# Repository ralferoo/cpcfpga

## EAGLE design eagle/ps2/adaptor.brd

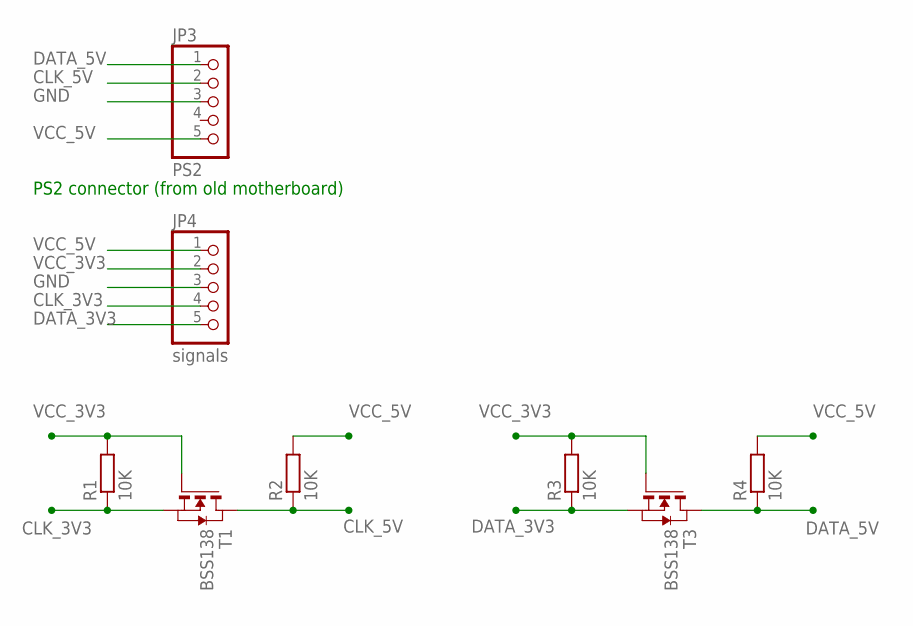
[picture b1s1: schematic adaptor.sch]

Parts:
JP3: PS2; 1X05
JP4: signals; 1X05
R1, R2, R3, R4: 10K; R0805
T1, T3: BSS138; SOT-23

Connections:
CLK_3V3: JP4.4, R1.1, T1.2 (S)
CLK_5V: JP3.2, R2.1, T1.1 (D)
DATA_3V3: JP4.5, R3.1, T3.2 (S)
DATA_5V: JP3.1, R4.1, T3.1 (D)
GND: JP3.3, JP4.3
VCC_3V3: JP4.2, R1.2, R3.2, T1.3 (G), T3.3 (G)
VCC_5V: JP3.5, JP4.1, R2.2, R4.2

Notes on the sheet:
PS2 connector (from old motherboard)

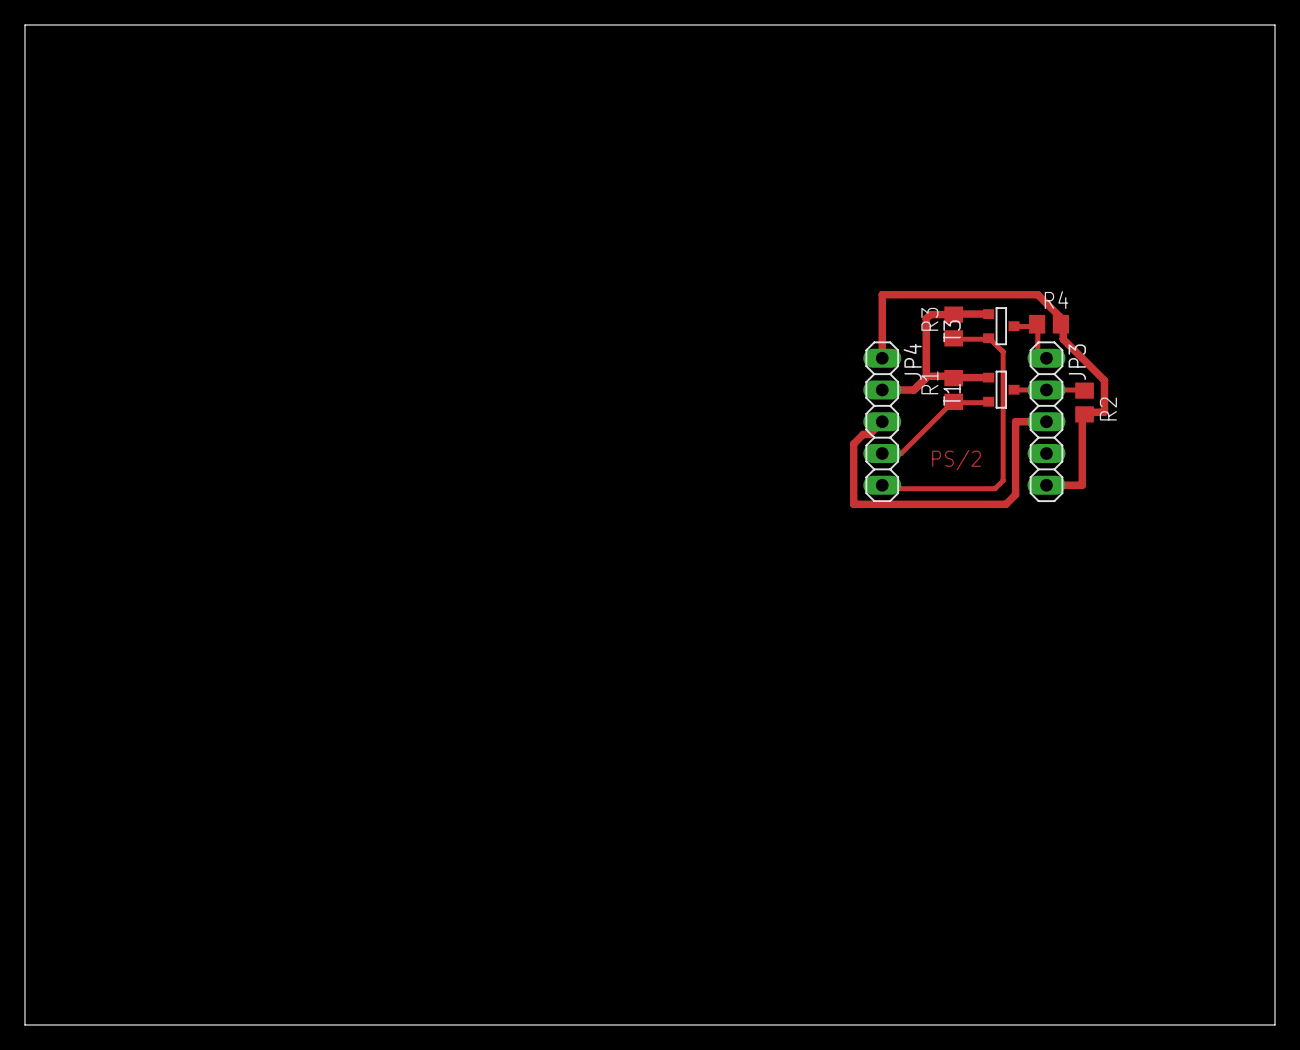
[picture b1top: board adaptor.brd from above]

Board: 2 copper layers, 100.0 x 80.0 mm, 8 parts (0 on the bottom side), 7 nets.

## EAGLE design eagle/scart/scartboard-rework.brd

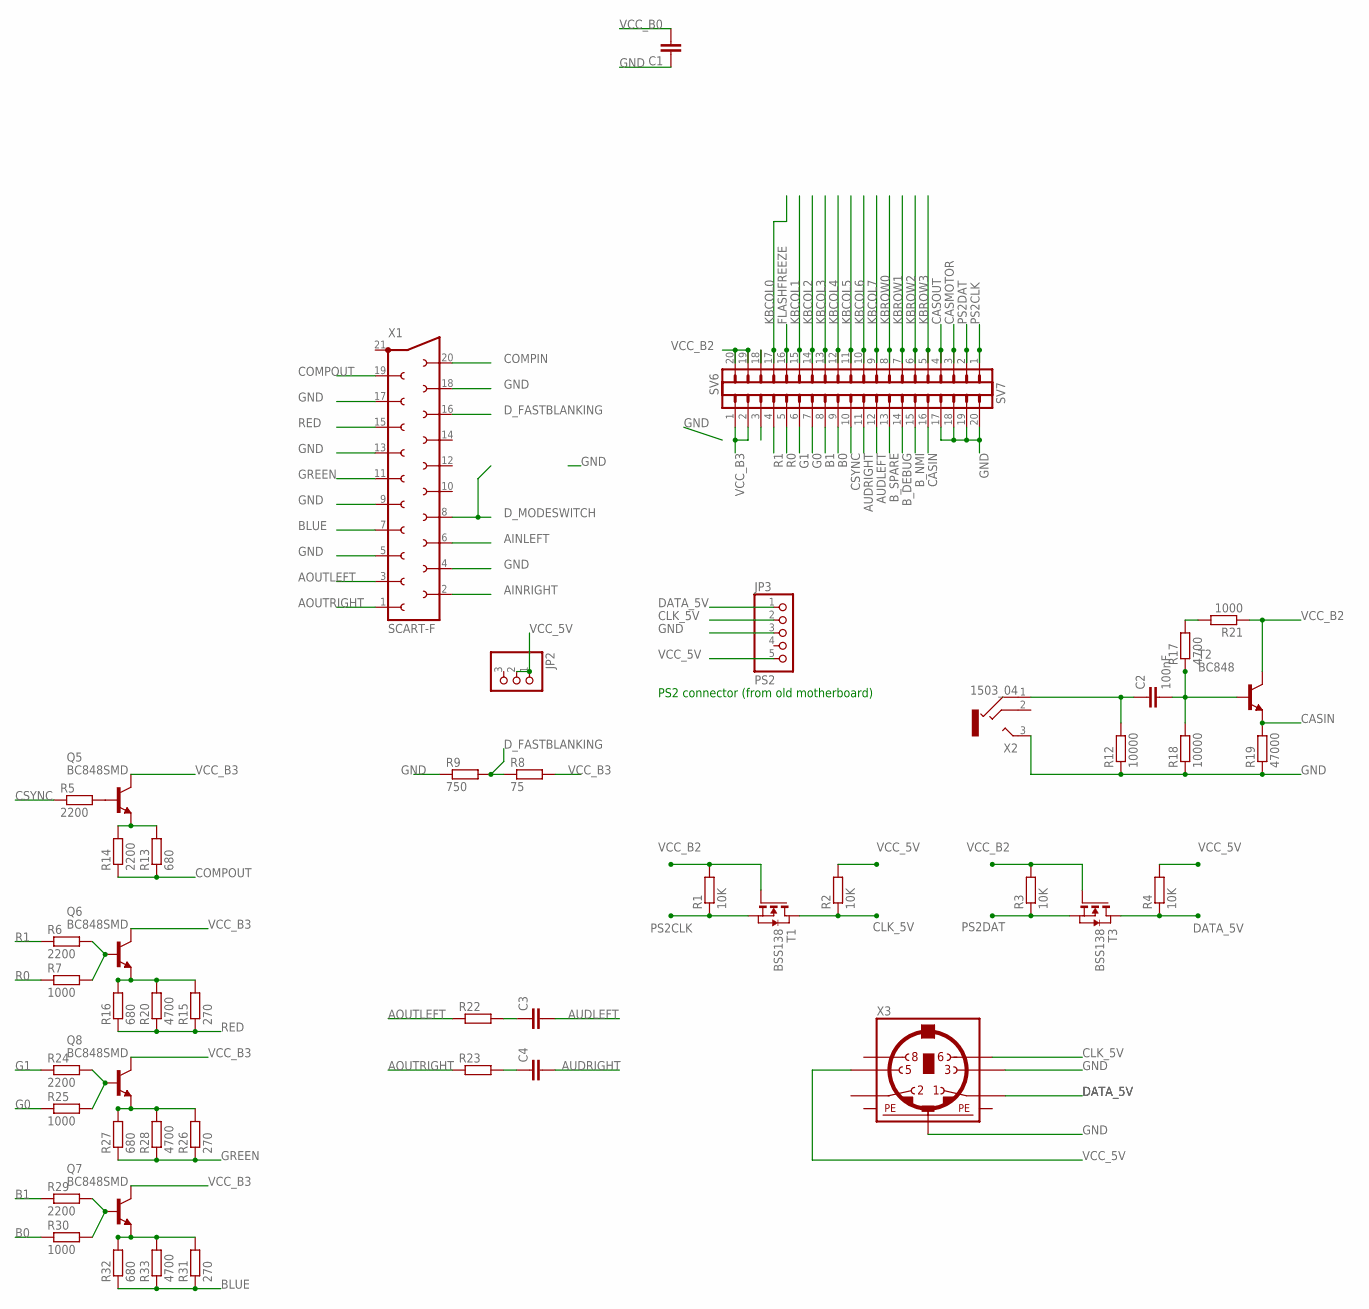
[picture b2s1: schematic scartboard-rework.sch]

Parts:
C1, C3, C4: C-EUC0603; C0603
C2: 100nF; C0603
JP2: PINHD-1X3; 1X03
JP3: PS2; 1X05
Q5, Q6, Q7, Q8: BC848SMD; SOT23
R1, R2, R3, R4: 10K; R0805
R5, R6, R14, R24, R29: 2200; R0805
R7, R21, R25, R30: 1000; R0805
R8: 75; R0805
R9: 750; R0805
R12, R18: 10000; R0805
R13, R16, R27, R32: 680; R0805
R15, R26, R31: 270; R0805
R17, R20, R28, R33: 4700; R0805
R19: 47000; R0805
R22, R23: R-EU_M0805; M0805
SV6, SV7: MA20-1
T1, T3: BSS138; SOT-23
T2: BC848; SOT23
X1: SCART-F
X2: 1503_04
X3: MINI_DIN_6; M_DIN6

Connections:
AINLEFT: X1.6
AINRIGHT: X1.2
AOUTLEFT: R22.1, X1.3
AOUTRIGHT: R23.1, X1.1
AUDLEFT: C3.2, SV7.12
AUDRIGHT: C4.2, SV7.11
B0: R30.1, SV7.9
B1: R29.1, SV7.8
BLUE: R31.1, R32.1, R33.1, X1.7
B_DEBUG: SV7.14
B_NMI: SV7.15
B_SPARE: SV7.13
CASIN: R19.2, SV7.16, T2.2 (E)
CASMOTOR: SV6.3
CASOUT: SV6.4
CLK_5V: JP3.2, R2.1, T1.1 (D), X3.6
COMPIN: X1.20
COMPOUT: R13.1, R14.1, X1.19
CSYNC: R5.1, SV7.10
DATA_5V: JP3.1, R4.1, T3.1 (D), X3.1
D_FASTBLANKING: R8.1, R9.2, X1.16
D_MODESWITCH: X1.8
FLASHFREEZE: SV6.16
G0: R25.1, SV7.7
G1: R24.1, SV7.6
GND: C1.1, JP3.3, R9.1, R12.1, R18.1, R19.1, SV7.17, SV7.18, SV7.19, SV7.20, X1.4, X1.5, X1.9, X1.13, X1.17, X1.18, X2.3 (2), X3.3, X3.SH2 (PE2)
GREEN: R26.1, R27.1, R28.1, X1.11
KBCOL0: SV6.17
KBCOL1: SV6.15
KBCOL2: SV6.14
KBCOL3: SV6.13
KBCOL4: SV6.12
KBCOL5: SV6.11
KBCOL6: SV6.10
KBCOL7: SV6.9
KBROW0: SV6.8
KBROW1: SV6.7
KBROW2: SV6.6
KBROW3: SV6.5
unnamed: Q5.2 (E), R13.2, R14.2
unnamed: Q6.1 (B), R6.2, R7.2
unnamed: Q5.1 (B), R5.2
unnamed: Q6.2 (E), R15.2, R16.2, R20.2
unnamed: C2.2, R17.1, R18.2, T2.1 (B)
unnamed: Q8.1 (B), R24.2, R25.2
unnamed: Q8.2 (E), R26.2, R27.2, R28.2
unnamed: Q7.1 (B), R29.2, R30.2
unnamed: Q7.2 (E), R31.2, R32.2, R33.2
unnamed: R17.2, R21.2
unnamed: C2.1, R12.2, X2.1
unnamed: C3.1, R22.2
unnamed: C4.1, R23.2
PE1: X3.SH1 (PE1)
PE3: X3.SH3 (PE3)
PS2CLK: R1.1, SV6.1, T1.2 (S)
PS2DAT: R3.1, SV6.2, T3.2 (S)
R0: R7.1, SV7.5
R1: R6.1, SV7.4
RED: R15.1, R16.1, R20.1, X1.15
VCC_5V: JP2.1, JP2.2, JP3.5, R2.2, R4.2, X3.5
VCC_B0: C1.2
VCC_B2: R1.2, R3.2, R21.1, SV6.19, SV6.20, T1.3 (G), T2.3 (C), T3.3 (G)
VCC_B3: Q5.3 (C), Q6.3 (C), Q7.3 (C), Q8.3 (C), R8.2, SV7.1, SV7.2

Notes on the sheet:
PS2 connector (from old motherboard)

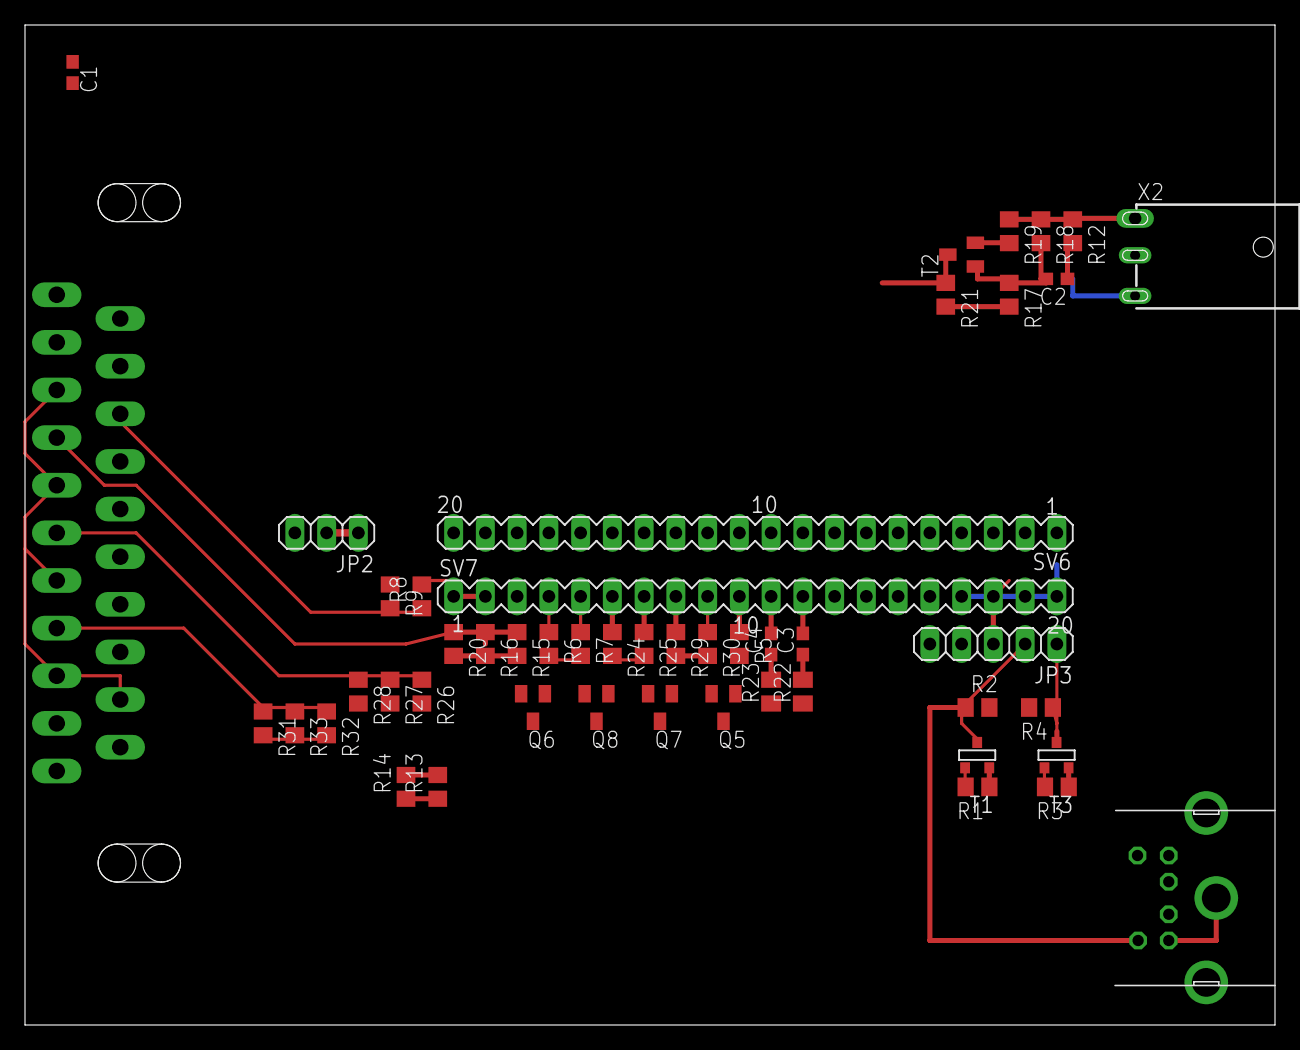
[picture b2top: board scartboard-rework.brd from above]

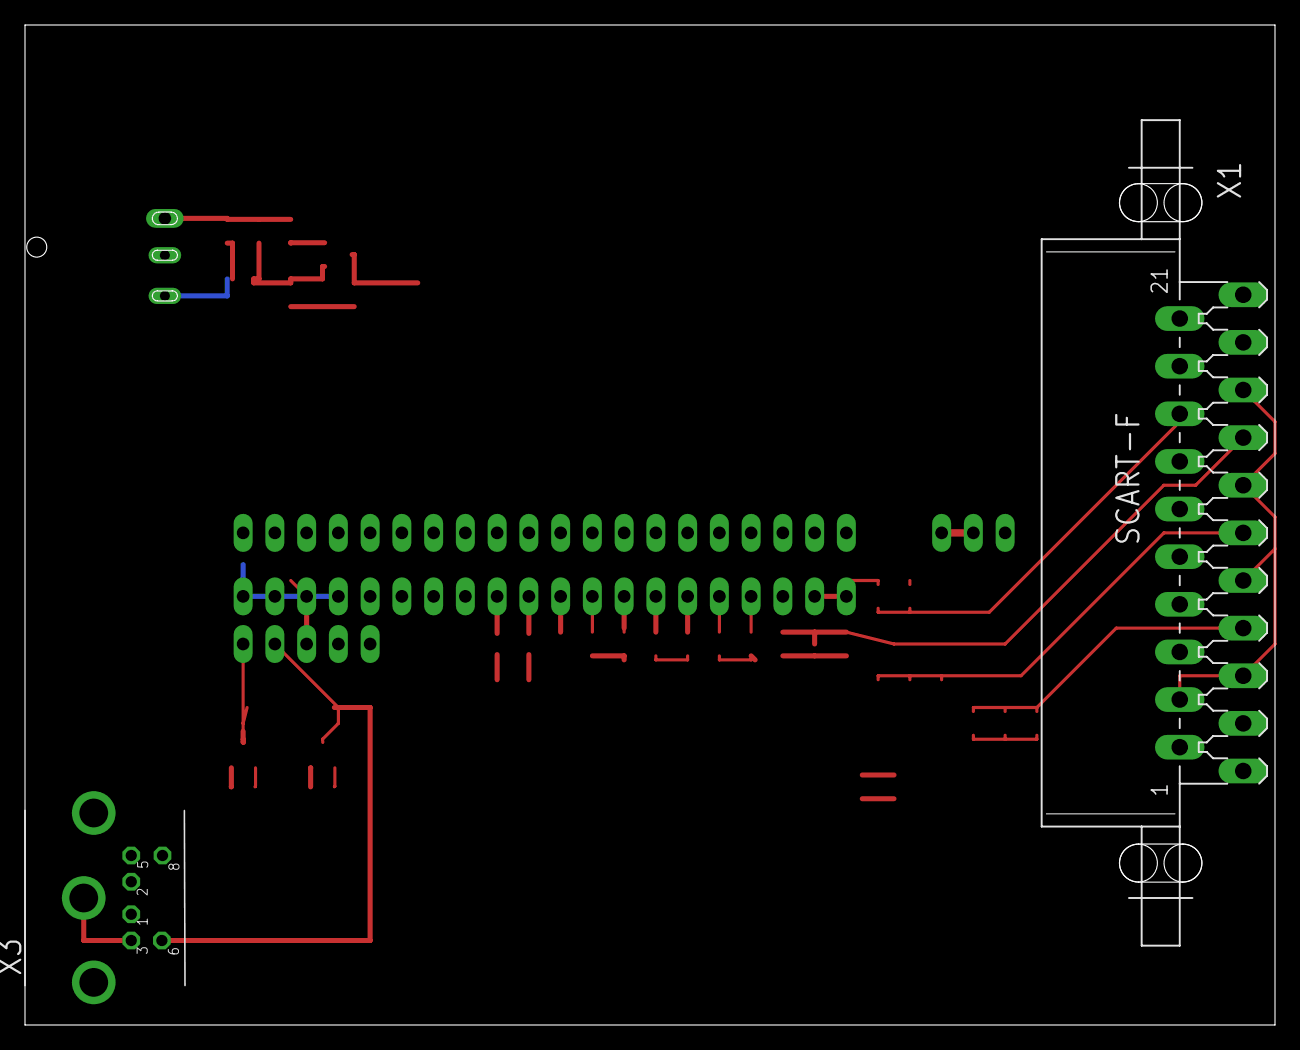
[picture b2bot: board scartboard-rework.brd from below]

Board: 2 copper layers, 100.0 x 80.0 mm, 49 parts (2 on the bottom side), 38 nets.

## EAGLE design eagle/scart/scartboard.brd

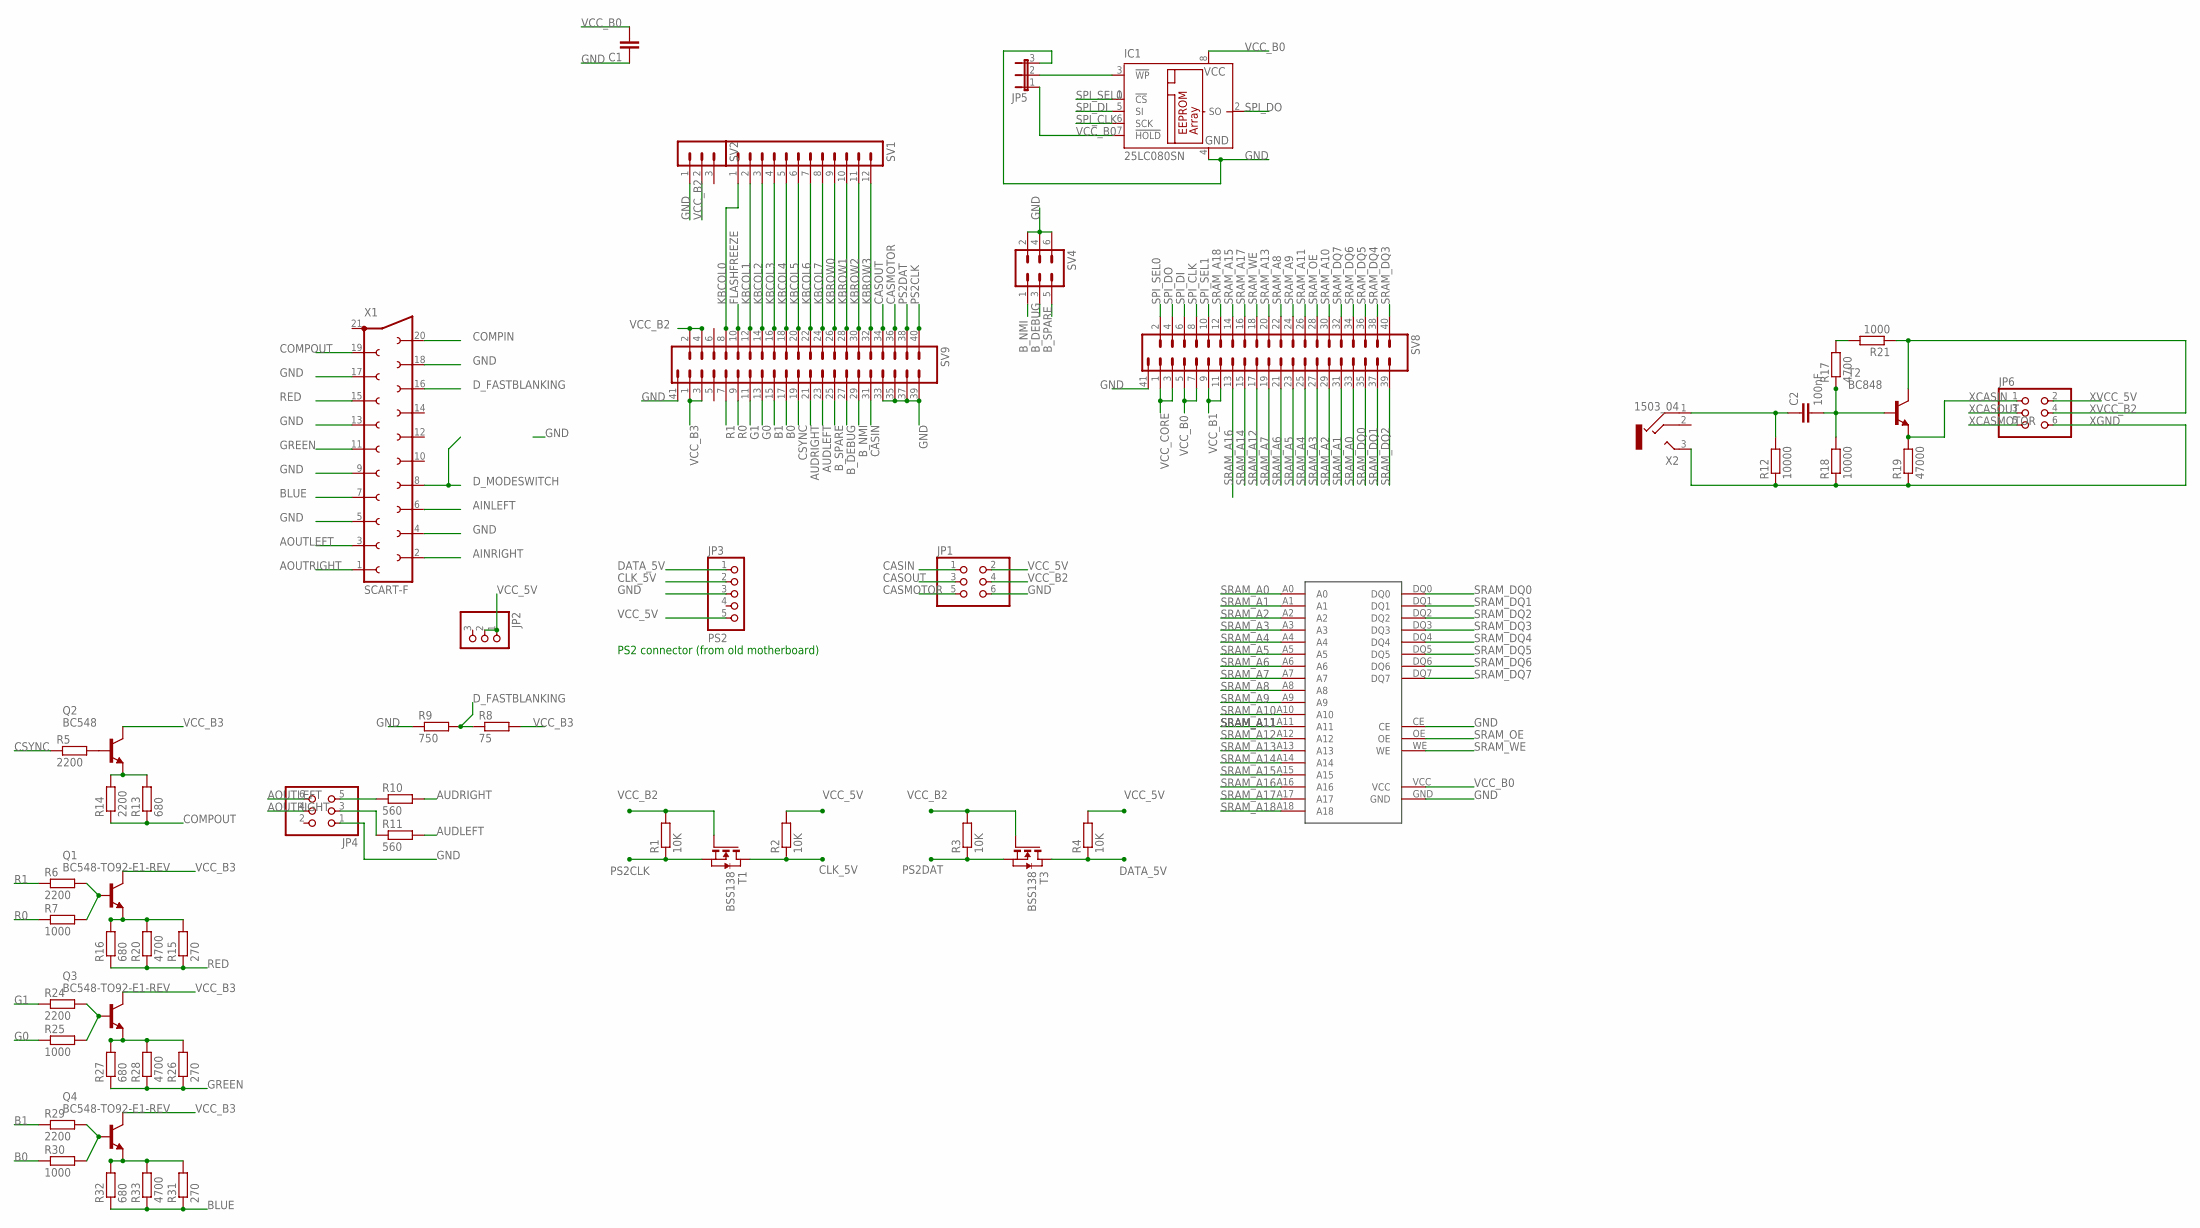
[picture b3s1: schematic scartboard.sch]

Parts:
C1: C-EUC0603; C0603
C2: 100nF; C0603
IC1: 25LC080SN; SO-08
JP1, JP4, JP6: PINHD-2X3; 2X03
JP2: PINHD-1X3; 1X03
JP3: PS2; 1X05
JP5: JP2E; JP2
Q1, Q3, Q4: BC548-TO92-E1-REV; TO92-E1-REV
Q2: BC548; TO92-EBC
R1, R2, R3, R4: 10K; R0805
R5, R6, R14, R24, R29: 2200; R0805
R7, R21, R25, R30: 1000; R0805
R8: 75; R0805
R9: 750; R0805
R10, R11: 560; R0805
R12, R18: 10000; R0805
R13, R16, R27, R32: 680; R0805
R15, R26, R31: 270; R0805
R17, R20, R28, R33: 4700; R0805
R19: 47000; R0805
SV1: MA12-1
SV2: MA03-1
SV4: MA03-2
SV8, SV9: ACTEL_HDR
T1, T3: BSS138; SOT-23
T2: BC848; SOT23
U$1: AS6C4008; SOP32
X1: SCART-F
X2: 1503_04

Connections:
AINLEFT: X1.6
AINRIGHT: X1.2
AOUTLEFT: JP4.6, X1.3
AOUTRIGHT: JP4.4, X1.1
AUDLEFT: R11.2, SV9.23
AUDRIGHT: R10.2, SV9.21
B0: R30.1, SV9.17
B1: R29.1, SV9.15
BLUE: R31.1, R32.1, R33.1, X1.7
B_DEBUG: SV4.3, SV9.27
B_NMI: SV4.1, SV9.29
B_SPARE: SV4.5, SV9.25
CASIN: JP1.1, SV9.31
CASMOTOR: JP1.5, SV9.36
CASOUT: JP1.3, SV9.34
CLK_5V: JP3.2, R2.1, T1.1 (D)
COMPIN: X1.20
COMPOUT: R13.1, R14.1, X1.19
CSYNC: R5.1, SV9.19
DATA_5V: JP3.1, R4.1, T3.1 (D)
D_FASTBLANKING: R8.1, R9.2, X1.16
D_MODESWITCH: X1.8
FLASHFREEZE: SV9.10
G0: R25.1, SV9.13
G1: R24.1, SV9.11
GND: C1.1, IC1.4 (GND), JP1.6, JP3.3, JP4.1, JP5.3, R9.1, SV2.1, SV4.2, SV4.4, SV4.6, SV8.41, SV9.33, SV9.35, SV9.37, SV9.39, SV9.41, U$1.CE, U$1.GND, X1.4, X1.5, X1.9, X1.13, X1.17, X1.18
GREEN: R26.1, R27.1, R28.1, X1.11
KBCOL0: SV1.1, SV9.8
KBCOL1: SV1.2, SV9.12
KBCOL2: SV1.3, SV9.14
KBCOL3: SV1.4, SV9.16
KBCOL4: SV1.5, SV9.18
KBCOL5: SV1.6, SV9.20
KBCOL6: SV1.7, SV9.22
KBCOL7: SV1.8, SV9.24
KBROW0: SV1.9, SV9.26
KBROW1: SV1.10, SV9.28
KBROW2: SV1.11, SV9.30
KBROW3: SV1.12, SV9.32
unnamed: Q2.E, R13.2, R14.2
unnamed: Q1.2 (B), R6.2, R7.2
unnamed: Q2.B, R5.2
unnamed: JP4.5, R10.1
unnamed: JP4.3, R11.1
unnamed: Q1.3 (E), R15.2, R16.2, R20.2
unnamed: IC1.3 (!WP), JP5.2
unnamed: C2.2, R17.1, R18.2, T2.1 (B)
unnamed: Q3.2 (B), R24.2, R25.2
unnamed: Q3.3 (E), R26.2, R27.2, R28.2
unnamed: Q4.2 (B), R29.2, R30.2
unnamed: Q4.3 (E), R31.2, R32.2, R33.2
unnamed: R17.2, R21.2
unnamed: C2.1, R12.2, X2.1
PS2CLK: R1.1, SV9.40, T1.2 (S)
PS2DAT: R3.1, SV9.38, T3.2 (S)
R0: R7.1, SV9.9
R1: R6.1, SV9.7
RED: R15.1, R16.1, R20.1, X1.15
SPI_CLK: IC1.6 (SCK), SV8.8
SPI_DI: IC1.5 (SI), SV8.6
SPI_DO: IC1.2 (SO), SV8.4
SPI_SEL0: IC1.1 (!CS), SV8.2
SPI_SEL1: SV8.10
SRAM_A0: SV8.33, U$1.A0
SRAM_A1: SV8.31, U$1.A1
SRAM_A2: SV8.29, U$1.A2
SRAM_A3: SV8.27, U$1.A3
SRAM_A4: SV8.25, U$1.A4
SRAM_A5: SV8.23, U$1.A5
SRAM_A6: SV8.21, U$1.A6
SRAM_A7: SV8.19, U$1.A7
SRAM_A8: SV8.22, U$1.A8
SRAM_A9: SV8.24, U$1.A9
SRAM_A10: SV8.30, U$1.A10
SRAM_A11: SV8.26, U$1.A11
SRAM_A12: SV8.17, U$1.A12
SRAM_A13: SV8.20, U$1.A13
SRAM_A14: SV8.15, U$1.A14
SRAM_A15: SV8.14, U$1.A15
SRAM_A16: SV8.13, U$1.A16
SRAM_A17: SV8.16, U$1.A17
SRAM_A18: SV8.12, U$1.A18
SRAM_DQ0: SV8.35, U$1.DQ0
SRAM_DQ1: SV8.37, U$1.DQ1
SRAM_DQ2: SV8.39, U$1.DQ2
SRAM_DQ3: SV8.40, U$1.DQ3
SRAM_DQ4: SV8.38, U$1.DQ4
SRAM_DQ5: SV8.36, U$1.DQ5
SRAM_DQ6: SV8.34, U$1.DQ6
SRAM_DQ7: SV8.32, U$1.DQ7
SRAM_OE: SV8.28, U$1.OE
SRAM_WE: SV8.18, U$1.WE
VCC_5V: JP1.2, JP2.1, JP2.2, JP3.5, R2.2, R4.2
VCC_B0: C1.2, IC1.7 (!HOLD), IC1.8 (VCC), JP5.1, SV8.5, SV8.7, U$1.VCC
VCC_B1: SV8.9, SV8.11
VCC_B2: JP1.4, R1.2, R3.2, SV2.2, SV9.2, SV9.4, T1.3 (G), T3.3 (G)
VCC_B3: Q1.1 (C), Q2.C, Q3.1 (C), Q4.1 (C), R8.2, SV9.1, SV9.3
VCC_CORE: SV8.1, SV8.3
XCASIN: JP6.1, R19.2, T2.2 (E)
XCASMOTOR: JP6.5
XCASOUT: JP6.3
XGND: JP6.6, R12.1, R18.1, R19.1, X2.3 (2)
XVCC_5V: JP6.2
XVCC_B2: JP6.4, R21.1, T2.3 (C)

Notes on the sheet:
PS2 connector (from old motherboard)

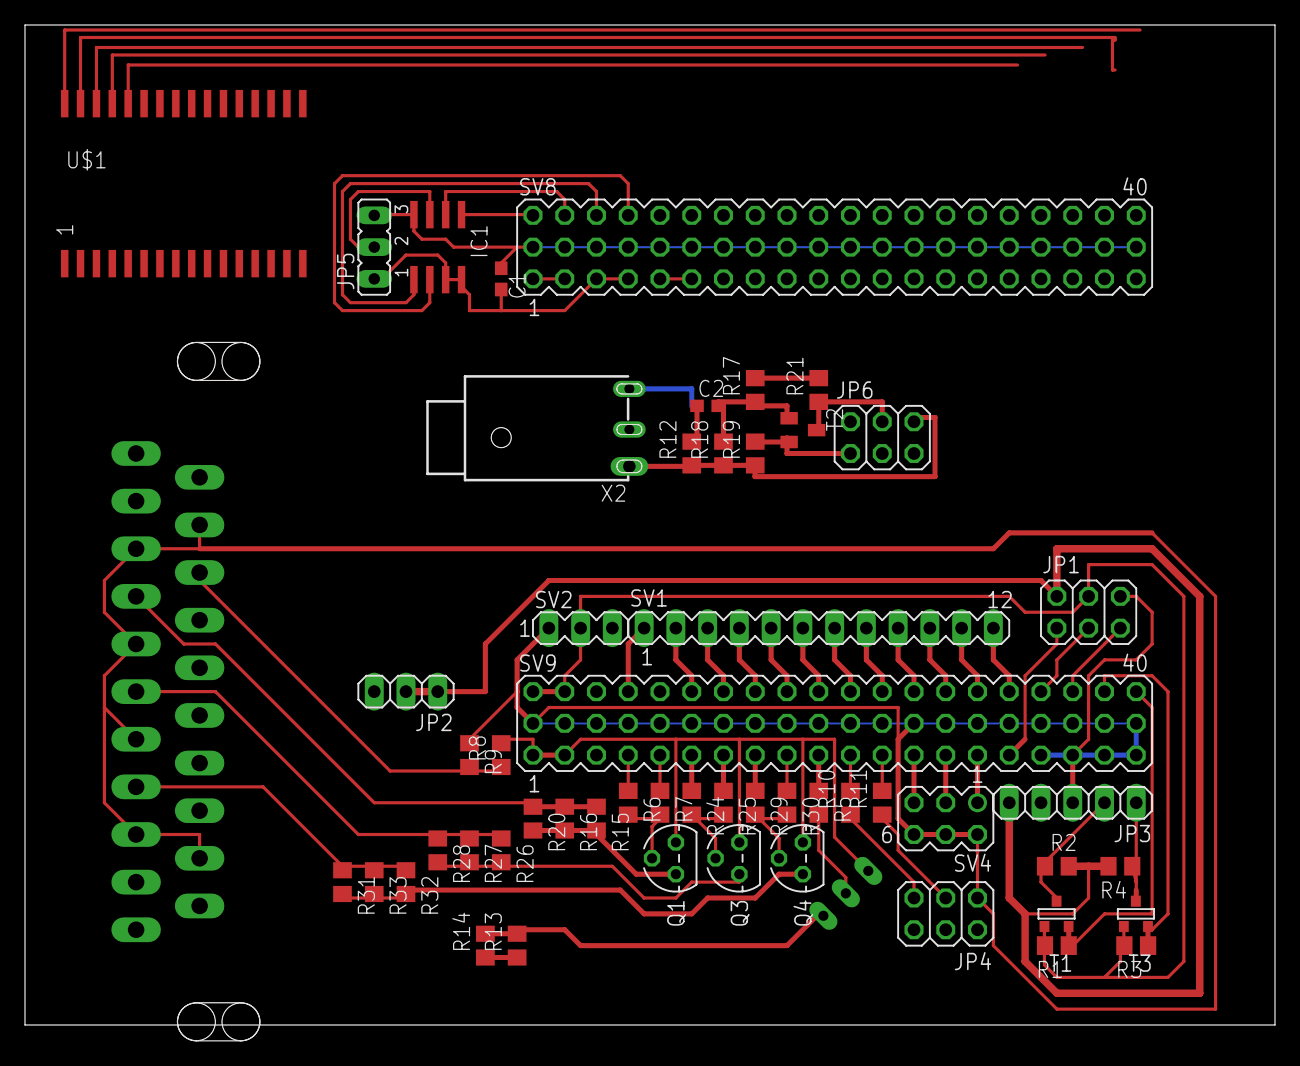
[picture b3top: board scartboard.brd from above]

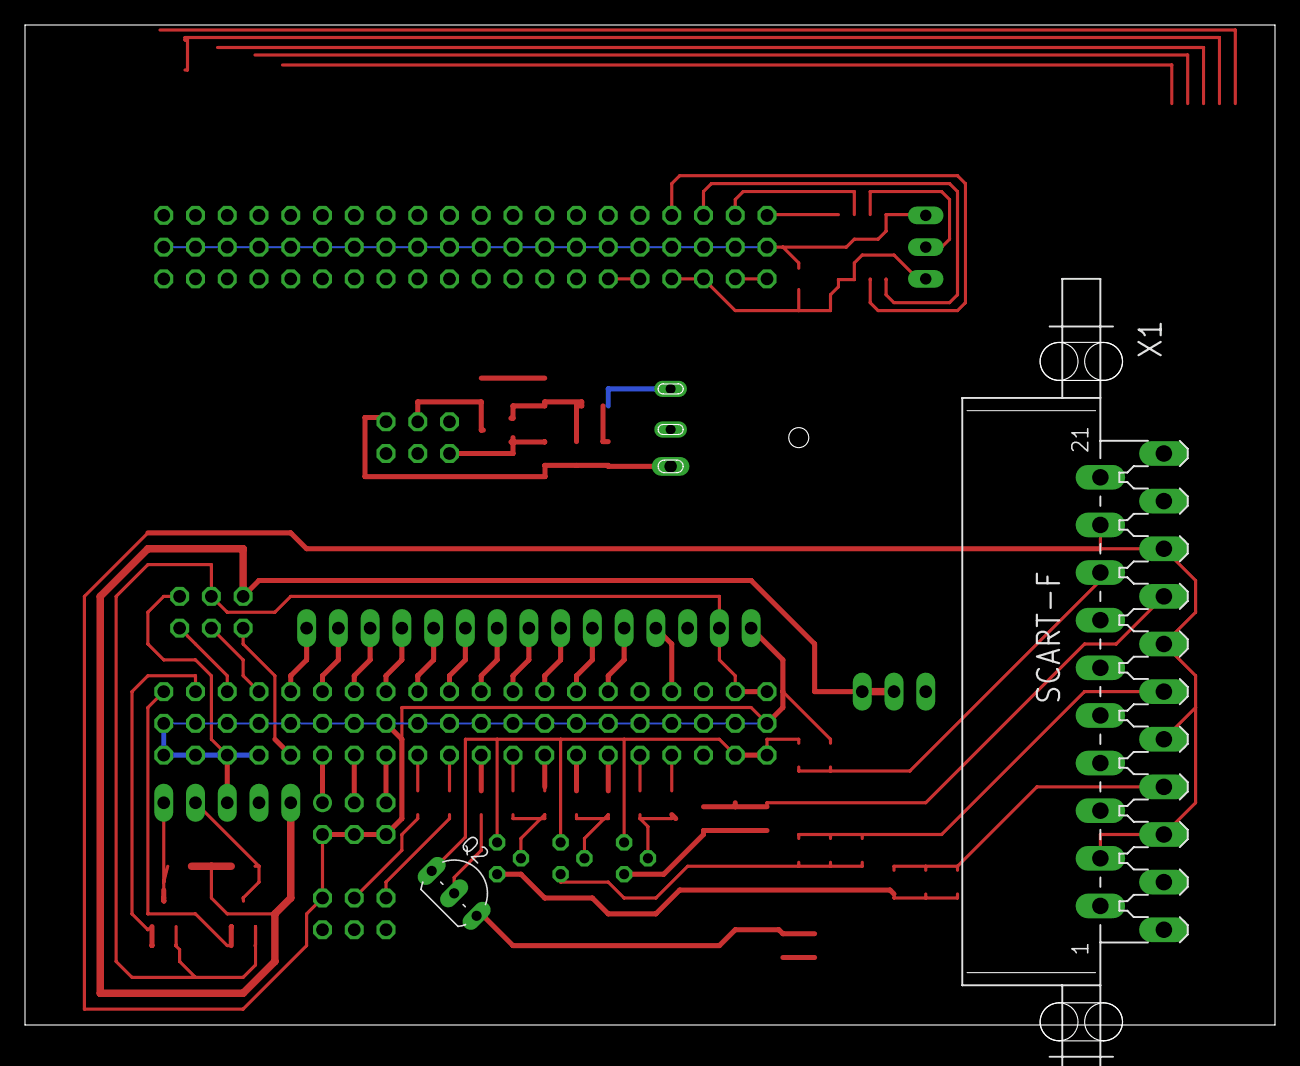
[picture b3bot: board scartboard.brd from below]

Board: 2 copper layers, 100.0 x 81.3 mm, 55 parts (2 on the bottom side), 95 nets.

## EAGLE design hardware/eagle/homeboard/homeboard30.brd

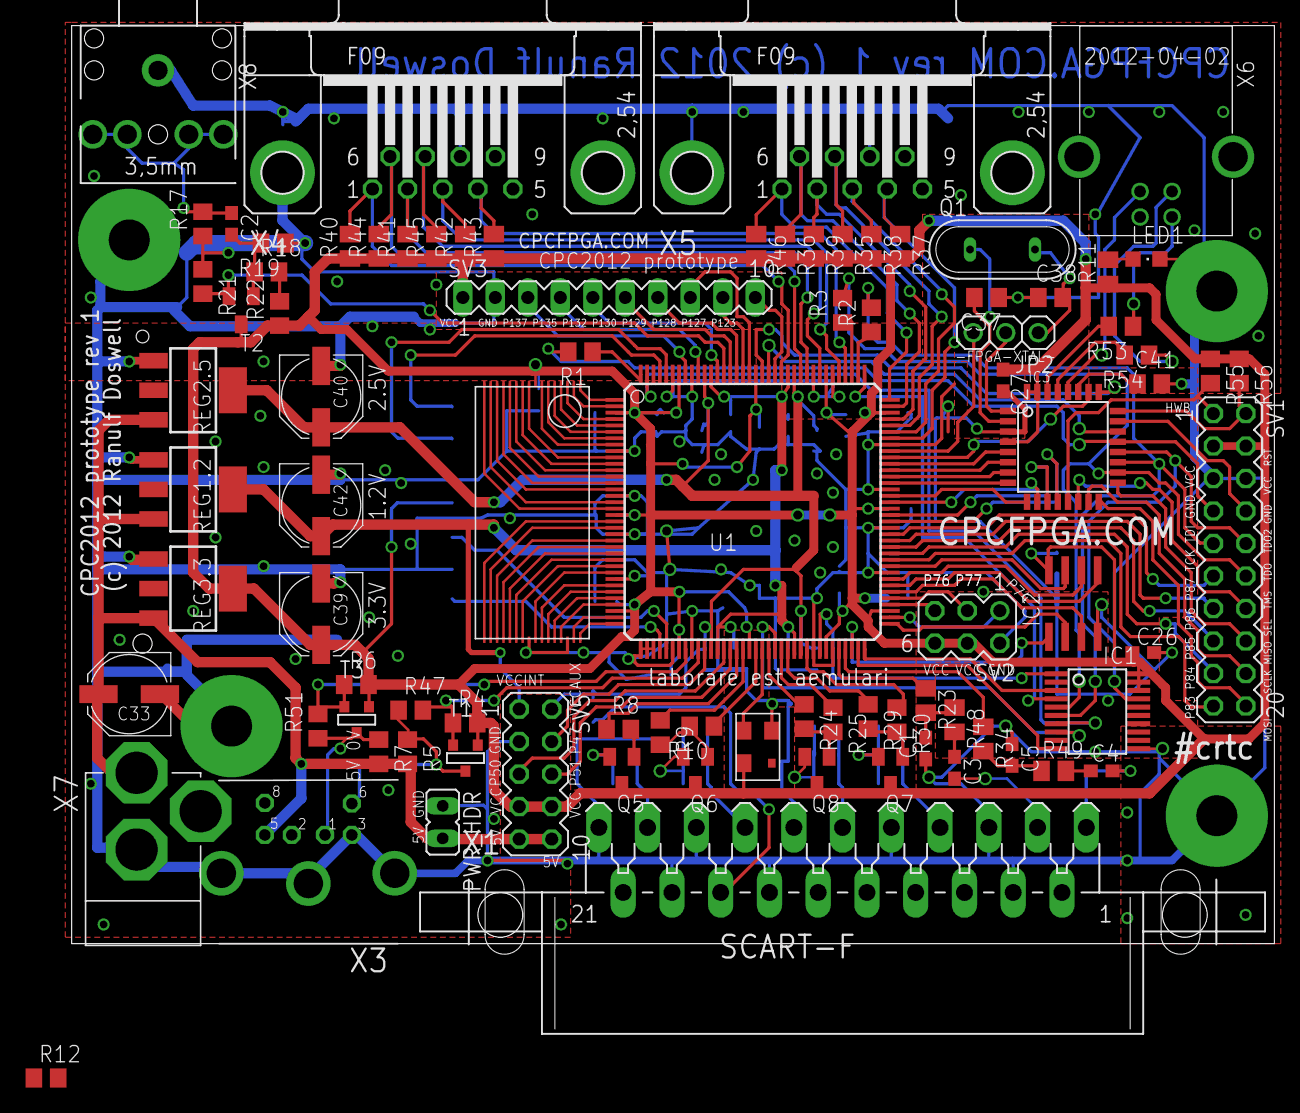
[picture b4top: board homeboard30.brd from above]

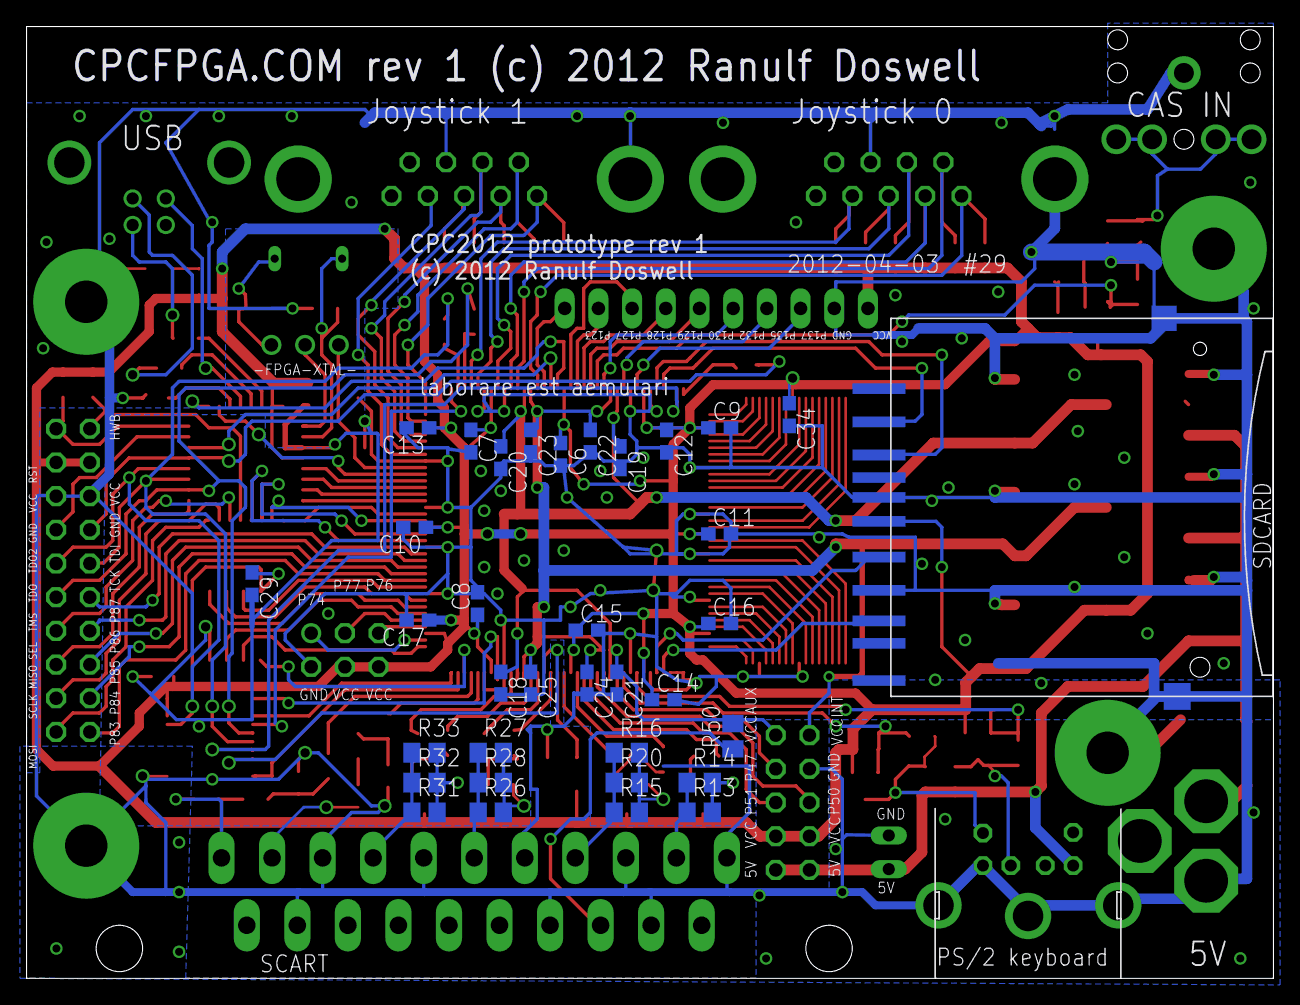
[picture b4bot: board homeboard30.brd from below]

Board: 2 copper layers, 94.0 x 71.8 mm, 127 parts (34 on the bottom side), 154 nets.

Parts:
C1, C2, C3, C4, C5, C6, C7, C8, C9, C10, C11, C12, C13, C14, C15, C16, C17, C18, C19, C20, C21, C22, C23, C24, C25, C26, C27, C29, C34: 100nF; C0603
C33, C39, C40, C42: 100u; PANASONIC_D
C37, C38: 20pF; C0805
C41: 1uF; C0805
IC1: XCF02S; VO20
IC2: 25LC080SN; SO-08
IC3: ATMEGA32U2-TQFP; TQFP32-08
JP2: 1X03
LED1: 20mA; CHIPLED_0805
PWR_HDR: JP1
Q1: QS
Q5, Q6, Q7, Q8: BC848SMD; SOT23
R1, R2, R3: 100; R0805
R4, R5, R6, R7, R10, R22, R25, R30: 1000; R0805
R8, R9, R14, R24, R29: 2200; R0805
R11, R23, R34: 75; M0805
R12, R21: 47000; R0805
R13: 680; R0805
R15, R20, R26, R28, R31, R33: NC; R0805
R16, R27, R32: 180; R0805
R17, R19: 10000; R0805
R18, R55, R56: 4700; R0805
R35, R36, R37, R38, R39, R40, R41, R42, R43, R44, R45, R46: M0805
R47, R51: 270; R0805
R48, R49: 2200; M0805
R50: 0R; M0805
R53, R54: 22; R0805
REG1.2: 1.2V; SOT223
REG2.5: 2.5V; SOT223
REG3.3: 3.3V; SOT223
SV1: MA10-2
SV2: MA03-2
SV3: MA10-1
SV5: MA05-2
T1, T3: BSS138; SOT-23
T2: BC848; SOT23
U1: XC3S400TQ144; TQ144
U$1, U$7, U$8, U$9: GNDHOLE
U$2: TXO_7C; OSC_7C
U$3: SDMMCNOHOLE; SDCARD-NOHOLE
U$6: AS6C4008; TSOP32
X1: SCART-CLIP
X3: M_DIN6
X4, X5: F09HP
X6: MINI-USB_4P-85-32004-10X; 85-32004-10X
X7: DC21MMX; DC-21MM
X8: STEREOJACK; 20-0137

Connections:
AT_CLKO: IC3.22, U1.P124
AT_RESET: IC3.24, R56.2, SV1.2
B0: R30.1, U1.P63
B1: R29.1, U1.P60
CASIN: R21.2, T2.2, U1.P131
CLK16: U1.P56, U$2.OUT
CLK_5V: R5.1, R47.1, T1.1, X3.6
CSYNC: R8.1, U1.P52
DATA_5V: R7.1, R51.1, T3.1, X3.1
EMER_BOOT: IC3.13, R55.2, SV1.1
EXP_A: SV5.4, U1.P47
EXP_B: SV5.5, U1.P50
EXP_C: SV5.6, U1.P51
EXTCLK: JP2.3, U1.P100
FL_DI: IC2.5, U1.P79
FL_DO: IC2.2, U1.P73
FL_HOLD: IC2.7, U1.P82
FL_SCLK: IC2.6, U1.P80
FL_SEL: IC2.1, U1.P70
FL_WP: IC2.3, U1.P78
FPGA_AUDIO_LEFT: R23.1, U1.P68
FPGA_AUDIO_RIGHT: R34.1, U1.P69
G0: R25.1, U1.P59
G1: R24.1, U1.P57
GND: C1.1, C5.1, C6.2, C7.2, C8.2, C9.2, C10.2, C11.2, C12.2, C13.2, C14.2, C15.2, C16.2, C17.2, C18.2, C19.2, C20.2, C21.2, C22.2, C23.2, C24.2, C25.2, C26.2, C27.2, C29.2, C33.-, C34.2, C37.1, C38.1, C39.-, C40.-, C41.2, C42.-, IC1.11, IC2.4, IC3.3, LED1.C, PWR_HDR.1, R12.1, R17.1, R19.1, R21.1, REG1.2.1, REG2.5.1, REG3.3.1, SV1.5, SV1.6, SV2.2, SV3.2, SV5.3, U1.P9, U1.P16, U1.P22, U1.P29, U1.P37, U1.P38, U1.P39, U1.P42, U1.P45, U1.P64, U1.P67, U1.P81, U1.P88, U1.P94, U1.P101, U1.P114, U1.P117, U1.P136, U1.P139, U$1.GND, U$2.GND, U$3.3, U$3.6, U$3.MT1, U$3.MT3, U$6.P24, U$6.P30, U$7.GND, U$8.GND, U$9.GND, X1.4, X1.5, X1.9, X1.13, X1.14, X1.17, X1.18, X1.21, X3.3, X3.SH1, X3.SH2, X3.SH3, X4.8, X4.G1, X5.8, X5.G1, X7.3, X8.1
GPIO_PIN3: SV3.3, U1.P137
GPIO_PIN4: SV3.4, U1.P135
GPIO_PIN5: SV3.5, U1.P132
GPIO_PIN6: SV3.6, U1.P130
GPIO_PIN7: SV3.7, U1.P129
GPIO_PIN8: SV3.8, U1.P127
GPIO_PIN9: SV3.9, U1.P128
GPIO_PIN10: SV3.10, U1.P123
HDR_MISO: SV1.15, U1.P85
HDR_MOSI: SV1.19, U1.P83
HDR_SCLK: SV1.17, U1.P84
HDR_SEL: SV1.13, U1.P86
HDR_SPARE: SV1.11, U1.P87
JOY0_DOWN: R41.2, U1.P118, X4.2
JOY0_FIRE1: R45.2, U1.P116, X4.7
JOY0_FIRE2: R44.2, U1.P119, X4.6
JOY0_LEFT: R42.2, U1.P113, X4.3
JOY0_RIGHT: R43.2, U1.P112, X4.4
JOY0_UP: R40.2, U1.P122, X4.1
JOY1_DOWN: R39.1, U1.P105, X5.2
JOY1_FIRE1: R35.1, U1.P104, X5.7
JOY1_FIRE2: R36.1, U1.P107, X5.6
JOY1_LEFT: R38.1, U1.P103, X5.3
JOY1_RIGHT: R37.1, U1.P102, X5.4
JOY1_UP: R46.1, U1.P108, X5.1
unnamed: IC3.1, JP2.2
unnamed: C41.1, IC3.27
unnamed: LED1.A, R11.2
unnamed: C37.2, IC3.2, Q1.1
unnamed: C38.2, JP2.1, Q1.2
unnamed: IC1.3, U1.P72
unnamed: R53.1, X6.2
unnamed: IC1.10, U1.P71
unnamed: R2.1, U1.P110
unnamed: IC1.7, U1.P143
unnamed: R1.1, U1.P144
unnamed: R3.1, U1.P111
unnamed: IC3.29, R54.2
unnamed: C1.2, R23.2, R48.1
unnamed: C3.1, R48.2
unnamed: Q6.1, R9.2, R10.2
unnamed: Q6.2, R15.2, R16.2, R20.2
unnamed: Q8.1, R24.2, R25.2
unnamed: Q8.2, R26.2, R27.2, R28.2
unnamed: Q7.1, R29.2, R30.2
unnamed: Q7.2, R31.2, R32.2, R33.2
unnamed: Q5.2, R13.2, R14.2
unnamed: C2.2, R12.2, R18.1, R19.2, T2.1
unnamed: C2.1, R17.2, X8.2, X8.3, X8.4, X8.5
unnamed: R18.2, R22.2
unnamed: Q5.1, R8.2
unnamed: C4.1, R49.2
unnamed: C5.2, R34.2, R49.1
unnamed: R54.1, X6.3
unnamed: IC3.30, R53.2
unnamed: IC3.28, X6.4
PC2: IC3.5, U1.P98
PC4: IC3.26, U1.P99
PC5: IC3.25, U1.P125
PD0: IC3.6, U1.P97
PD1: IC3.7, U1.P96
PD2: IC3.8, U1.P95
PD3: IC3.9, U1.P93
PD4: IC3.10, U1.P92
PD5: IC3.11, U1.P90
PD6: IC3.12, U1.P89
PROM_DO: IC1.1, U1.P65
PROM_INITB: IC1.8, U1.P58
PS2CLK: R4.1, R47.2, T1.2, U1.P46
PS2DAT: R6.1, R51.2, T3.2, U1.P44
R0: R10.1, U1.P55
R1: R9.1, U1.P53
SCART_BLANKING: R50.1, X1.16
SCART_BLUE: R31.1, R32.1, R33.1, X1.7
SCART_COMP: R13.1, R14.1, X1.19
SCART_GREEN: R26.1, R27.1, R28.1, X1.11
SCART_LEFT: C3.2, X1.3
SCART_RED: R15.1, R16.1, R20.1, X1.15
SCART_RIGHT: C4.2, X1.1
SD_CLK: U1.P41, U$3.5
SD_CS: U1.P141, U$3.1
SD_DI: U1.P140, U$3.2
SD_DO: U1.P40, U$3.7
SPI_MISO: IC3.17, SV1.16
SPI_MOSI: IC3.16, SV1.20
SPI_SCLK: IC3.15, SV1.18
SPI_SEL: IC3.14, SV1.14
SRAM_A0: U1.P24, U$6.P20
SRAM_A1: U1.P23, U$6.P19
SRAM_A2: U1.P21, U$6.P18
SRAM_A3: U1.P20, U$6.P17
SRAM_A4: U1.P18, U$6.P16
SRAM_A5: U1.P17, U$6.P15
SRAM_A6: U1.P15, U$6.P14
SRAM_A7: U1.P14, U$6.P13
SRAM_A8: U1.P4, U$6.P3
SRAM_A9: U1.P2, U$6.P2
SRAM_A10: U1.P35, U$6.P31
SRAM_A11: U1.P1, U$6.P1
SRAM_A12: U1.P13, U$6.P12
SRAM_A13: U1.P5, U$6.P4
SRAM_A14: U1.P12, U$6.P11
SRAM_A15: U1.P8, U$6.P7
SRAM_A16: U1.P11, U$6.P10
SRAM_A17: U1.P7, U$6.P6
SRAM_A18: U1.P10, U$6.P9
SRAM_D0: U1.P25, U$6.P21
SRAM_D1: U1.P26, U$6.P22
SRAM_D2: U1.P27, U$6.P23
SRAM_D3: U1.P28, U$6.P25
SRAM_D4: U1.P30, U$6.P26
SRAM_D5: U1.P31, U$6.P27
SRAM_D6: U1.P32, U$6.P28
SRAM_D7: U1.P33, U$6.P29
SRAM_OE: U1.P36, U$6.P32
SRAM_WE: U1.P6, U$6.P5
TCK: IC1.6, IC3.19, R2.2, SV1.9
TDI_FPGA: IC3.21, R1.2, SV1.7
TDO_EXP: IC3.23, SV1.8
TDO_FPGA: IC1.4, U1.P109
TDO_PROM: IC1.17, IC3.20, SV1.10
TMS: IC1.5, IC3.18, R3.2, SV1.12
VCC: C6.1, C7.1, C8.1, C9.1, C10.1, C11.1, C12.1, C13.1, C14.1, C15.1, C16.1, C17.1, C26.1, C27.1, C29.1, C34.1, C39.+, IC1.18, IC1.19, IC1.20, IC2.8, IC3.4, IC3.31, IC3.32, Q5.3, Q6.3, Q7.3, Q8.3, R4.2, R6.2, R11.1, R22.1, R35.2, R36.2, R37.2, R38.2, R39.2, R40.1, R41.1, R42.1, R43.1, R44.1, R45.1, R46.2, R55.1, R56.1, REG3.3.4, SV1.3, SV1.4, SV2.4, SV2.6, SV3.1, SV5.7, SV5.8, T1.3, T2.3, T3.3, U1.P3, U1.P19, U1.P34, U1.P43, U1.P54, U1.P66, U1.P75, U1.P91, U1.P106, U1.P115, U1.P126, U1.P138, U$2.VDD, U$3.4, U$6.P8
VCC5: C33.+, PWR_HDR.2, R5.2, R7.2, REG1.2.3, REG2.5.3, REG3.3.3, SV5.9, SV5.10, X3.5, X7.2
VCCAUX: C18.1, C19.1, C20.1, C21.1, C40.+, R50.2, REG2.5.4, SV5.2, U1.P48, U1.P62, U1.P120, U1.P134
VCCINT: C22.1, C23.1, C24.1, C25.1, C42.+, REG1.2.4, SV5.1, U1.P49, U1.P61, U1.P121, U1.P133
X3: SV2.5, U1.P76
X4: SV2.3, U1.P77
X8: SV2.1, U1.P74

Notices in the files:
hardware/eagle/homeboard/homeboard30.brd:
CPCFPGA.COM rev 1 (c) 2012 Ranulf Doswell
